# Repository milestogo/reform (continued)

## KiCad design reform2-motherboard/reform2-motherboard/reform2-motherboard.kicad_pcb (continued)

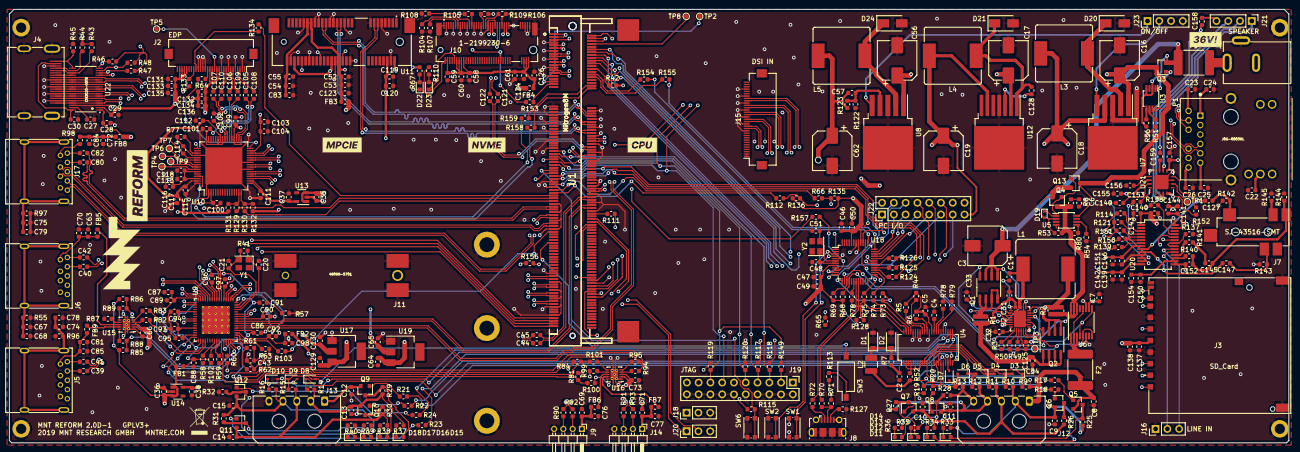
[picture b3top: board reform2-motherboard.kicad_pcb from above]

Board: 6 copper layers, 276.0 x 93.5 mm, 440 parts (0 on the bottom side), 466 nets.

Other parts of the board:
U1#2: Nitrogen8M; TE_1473149-4

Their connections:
+4V: U1#2.1, U1#2.2, U1#2.3, U1#2.4, U1#2.5, U1#2.6; also elsewhere on the board
BACKLIGHT_EN: U1#2.105; also elsewhere on the board
DAC_BCLK: U1#2.170; also elsewhere on the board
DAC_DIN: U1#2.166; also elsewhere on the board
DAC_DOUT: U1#2.178; also elsewhere on the board
DAC_MCLK: U1#2.176; also elsewhere on the board
DAC_RXFS: U1#2.168; also elsewhere on the board
DAC_SCL: U1#2.101; also elsewhere on the board
DAC_SDA: U1#2.103; also elsewhere on the board
DAC_TXFS: U1#2.172; also elsewhere on the board
EDP_SCL: U1#2.107; also elsewhere on the board
EDP_SDA: U1#2.109; also elsewhere on the board
ETH0_A+: U1#2.29; also elsewhere on the board
ETH0_A-: U1#2.27; also elsewhere on the board
ETH0_B+: U1#2.17; also elsewhere on the board
ETH0_B-: U1#2.15; also elsewhere on the board
ETH0_C+: U1#2.23; also elsewhere on the board
ETH0_C-: U1#2.21; also elsewhere on the board
ETH0_D+: U1#2.11; also elsewhere on the board
ETH0_D-: U1#2.9; also elsewhere on the board
ETH0_LED_LINK1: U1#2.83; also elsewhere on the board
ETH0_LED_LINK2: U1#2.81; also elsewhere on the board
ETH0_LED_RX: U1#2.79; also elsewhere on the board
GND: U1#2.7, U1#2.13, U1#2.19, U1#2.25, U1#2.31, U1#2.41, U1#2.44, U1#2.47, U1#2.50, U1#2.53, U1#2.56, U1#2.59, U1#2.62, U1#2.65, U1#2.68, U1#2.71, U1#2.74, U1#2.80, U1#2.94, U1#2.95, U1#2.98, U1#2.99, U1#2.104, U1#2.110, U1#2.111, U1#2.116, U1#2.117, U1#2.123, U1#2.129, U1#2.161, U1#2.167, U1#2.173, U1#2.179, U1#2.185, U1#2.191; also elsewhere on the board
HDMI_CEC: U1#2.197; also elsewhere on the board
HDMI_CLK+: U1#2.165; also elsewhere on the board
HDMI_CLK-: U1#2.163; also elsewhere on the board
HDMI_D0+: U1#2.171; also elsewhere on the board
HDMI_D0-: U1#2.169; also elsewhere on the board
HDMI_D1+: U1#2.177; also elsewhere on the board
HDMI_D1-: U1#2.175; also elsewhere on the board
HDMI_D2+: U1#2.183; also elsewhere on the board
HDMI_D2-: U1#2.181; also elsewhere on the board
HDMI_HPD: U1#2.199; also elsewhere on the board
HDMI_SCL: U1#2.195; also elsewhere on the board
HDMI_SDA: U1#2.193; also elsewhere on the board
IMX_JTAG_TCK: U1#2.73; also elsewhere on the board
IMX_JTAG_TDI: U1#2.75; also elsewhere on the board
IMX_JTAG_TMS: U1#2.77; also elsewhere on the board
IMX_RESETn: U1#2.87; also elsewhere on the board
IMX_UART1_RX: U1#2.126; also elsewhere on the board
IMX_UART1_TX: U1#2.128; also elsewhere on the board
IMX_UART2_RX: U1#2.122; also elsewhere on the board
IMX_UART2_TX: U1#2.124; also elsewhere on the board
LPC_MISO: U1#2.93; also elsewhere on the board
LPC_MOSI: U1#2.91; also elsewhere on the board
LPC_SCK: U1#2.97; also elsewhere on the board
LPC_SS0: U1#2.89; also elsewhere on the board
unnamed 349: U1#2.174; also elsewhere on the board
unnamed 368: U1#2.118; also elsewhere on the board
unnamed 384: U1#2.37; also elsewhere on the board
unnamed 385: U1#2.30; also elsewhere on the board
unnamed 386: U1#2.32; also elsewhere on the board
unnamed 387: U1#2.164; also elsewhere on the board
unnamed 388: U1#2.40; also elsewhere on the board
unnamed 389: U1#2.38; also elsewhere on the board
unnamed 390: U1#2.139; also elsewhere on the board
unnamed 392: U1#2.35; also elsewhere on the board
unnamed 397: U1#2.8; also elsewhere on the board
unnamed 399: U1#2.10; also elsewhere on the board
unnamed 400: U1#2.24; also elsewhere on the board
unnamed 401: U1#2.28; also elsewhere on the board
unnamed 402: U1#2.33; also elsewhere on the board
unnamed 403: U1#2.34; also elsewhere on the board
unnamed 404: U1#2.36; also elsewhere on the board
unnamed 405: U1#2.39; also elsewhere on the board
unnamed 406: U1#2.42; also elsewhere on the board
unnamed 407: U1#2.43; also elsewhere on the board
unnamed 408: U1#2.45; also elsewhere on the board
unnamed 409: U1#2.49; also elsewhere on the board
unnamed 410: U1#2.51; also elsewhere on the board
unnamed 411: U1#2.55; also elsewhere on the board
unnamed 412: U1#2.57; also elsewhere on the board
unnamed 413: U1#2.61; also elsewhere on the board
unnamed 414: U1#2.63; also elsewhere on the board
unnamed 415: U1#2.67; also elsewhere on the board
unnamed 416: U1#2.69; also elsewhere on the board
unnamed 417: U1#2.82; also elsewhere on the board
unnamed 418: U1#2.84; also elsewhere on the board
unnamed 419: U1#2.85; also elsewhere on the board
unnamed 420: U1#2.86; also elsewhere on the board
unnamed 421: U1#2.88; also elsewhere on the board
unnamed 422: U1#2.90; also elsewhere on the board
unnamed 423: U1#2.92; also elsewhere on the board
unnamed 424: U1#2.96; also elsewhere on the board
unnamed 425: U1#2.120; also elsewhere on the board
unnamed 426: U1#2.130; also elsewhere on the board
unnamed 427: U1#2.132; also elsewhere on the board
unnamed 428: U1#2.133; also elsewhere on the board
unnamed 429: U1#2.134; also elsewhere on the board
unnamed 430: U1#2.135; also elsewhere on the board
unnamed 431: U1#2.136; also elsewhere on the board
unnamed 432: U1#2.137; also elsewhere on the board
unnamed 433: U1#2.138; also elsewhere on the board
unnamed 434: U1#2.140; also elsewhere on the board
unnamed 435: U1#2.141; also elsewhere on the board
unnamed 436: U1#2.142; also elsewhere on the board
unnamed 437: U1#2.143; also elsewhere on the board
unnamed 438: U1#2.144; also elsewhere on the board
unnamed 439: U1#2.145; also elsewhere on the board
unnamed 440: U1#2.146; also elsewhere on the board
unnamed 441: U1#2.147; also elsewhere on the board
unnamed 442: U1#2.148; also elsewhere on the board
unnamed 443: U1#2.149; also elsewhere on the board
unnamed 444: U1#2.150; also elsewhere on the board
unnamed 445: U1#2.151; also elsewhere on the board
unnamed 446: U1#2.152; also elsewhere on the board
unnamed 447: U1#2.153; also elsewhere on the board
unnamed 448: U1#2.154; also elsewhere on the board
unnamed 449: U1#2.155; also elsewhere on the board
unnamed 450: U1#2.156; also elsewhere on the board
unnamed 451: U1#2.157; also elsewhere on the board
unnamed 452: U1#2.158; also elsewhere on the board
unnamed 453: U1#2.159; also elsewhere on the board
unnamed 454: U1#2.160; also elsewhere on the board
unnamed 455: U1#2.162; also elsewhere on the board
unnamed 456: U1#2.180; also elsewhere on the board
unnamed 457: U1#2.182; also elsewhere on the board
unnamed 458: U1#2.184; also elsewhere on the board
unnamed 459: U1#2.186; also elsewhere on the board
unnamed 460: U1#2.187; also elsewhere on the board
unnamed 461: U1#2.188; also elsewhere on the board
unnamed 462: U1#2.189; also elsewhere on the board
unnamed 463: U1#2.190; also elsewhere on the board
unnamed 464: U1#2.192; also elsewhere on the board
unnamed 465: U1#2.194; also elsewhere on the board
unnamed 466: U1#2.196; also elsewhere on the board
unnamed 467: U1#2.198; also elsewhere on the board
unnamed 468: U1#2.200; also elsewhere on the board
PCIE1_CLK_N: U1#2.60; also elsewhere on the board
PCIE1_CLK_P: U1#2.58; also elsewhere on the board
PCIE1_RX_N: U1#2.54; also elsewhere on the board
PCIE1_RX_P: U1#2.52; also elsewhere on the board
PCIE1_TX_N: U1#2.48; also elsewhere on the board
PCIE1_TX_P: U1#2.46; also elsewhere on the board
PCIE2_CLK_N: U1#2.66; also elsewhere on the board
PCIE2_CLK_P: U1#2.64; also elsewhere on the board
PCIE2_RX_N: U1#2.78; also elsewhere on the board
PCIE2_RX_P: U1#2.76; also elsewhere on the board
PCIE2_TX_N: U1#2.72; also elsewhere on the board
PCIE2_TX_P: U1#2.70; also elsewhere on the board
SD2_CD: U1#2.26; also elsewhere on the board
SD2_CLK: U1#2.22; also elsewhere on the board
SD2_CMD: U1#2.20; also elsewhere on the board
SD2_DATA0: U1#2.12; also elsewhere on the board
SD2_DATA1: U1#2.14; also elsewhere on the board
SD2_DATA2: U1#2.16; also elsewhere on the board
SD2_DATA3: U1#2.18; also elsewhere on the board
USB1_DN: U1#2.100; also elsewhere on the board
USB1_DP: U1#2.102; also elsewhere on the board
USB1_RX_N: U1#2.112; also elsewhere on the board
USB1_RX_P: U1#2.114; also elsewhere on the board
USB1_TX_N: U1#2.106; also elsewhere on the board
USB1_TX_P: U1#2.108; also elsewhere on the board
USB2_DN: U1#2.125; also elsewhere on the board
USB2_DP: U1#2.127; also elsewhere on the board
USB2_RX_N: U1#2.121; also elsewhere on the board
USB2_RX_P: U1#2.119; also elsewhere on the board
USB2_TX_N: U1#2.115; also elsewhere on the board
USB2_TX_P: U1#2.113; also elsewhere on the board
USB_RESETn: U1#2.131; also elsewhere on the board

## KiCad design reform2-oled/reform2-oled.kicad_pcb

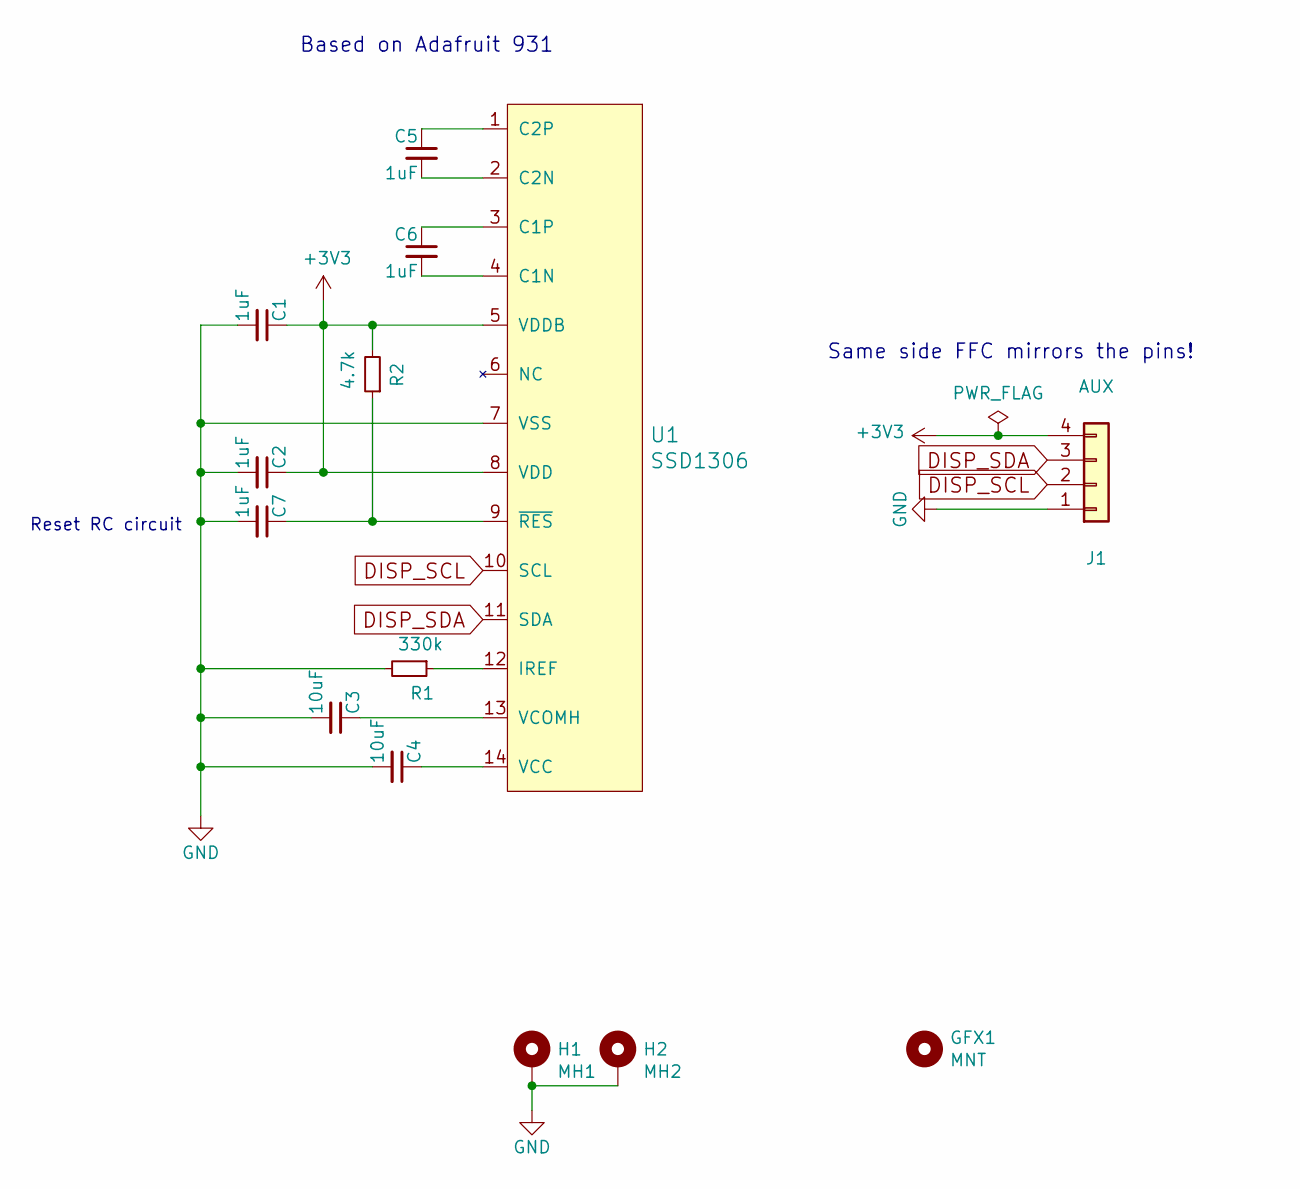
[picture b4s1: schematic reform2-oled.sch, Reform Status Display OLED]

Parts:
C1, C2, C5, C6, C7: 1uF; C_0603_1608Metric_Pad1.05x0.95mm_HandSolder
C3, C4: 10uF; C_0603_1608Metric_Pad1.05x0.95mm_HandSolder
GFX1: MNT; mntreform
H1: MH1; MountingHole_2.2mm_M2_Pad
H2: MH2; MountingHole_2.2mm_M2_Pad
J1: AUX; Molex_200528-0040_1x04-1MP_P1.00mm_Horizontal
R1: 330k; R_0603_1608Metric_Pad1.05x0.95mm_HandSolder
R2: 4.7k; R_0603_1608Metric_Pad1.05x0.95mm_HandSolder
U1: SSD1306; SSD1306_OLED-0.91-128x32

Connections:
+3V3: C1.1, C2.1, J1.4, R2.2, U1.5 (VDDB), U1.8 (VDD)
DISP_SCL: J1.2, U1.10 (SCL)
DISP_SDA: J1.3, U1.11 (SDA)
GND: C1.2, C2.2, C3.2, C4.2, C7.2, H1.1, H2.1, J1.1, R1.2, U1.7 (VSS)
unnamed: C3.1, U1.13 (VCOMH)
unnamed: C4.1, U1.14 (VCC)
unnamed: C5.1, U1.1 (C2P)
unnamed: C5.2, U1.2 (C2N)
unnamed: C6.1, U1.3 (C1P)
unnamed: C6.2, U1.4 (C1N)
unnamed: C7.1, R2.1, U1.9 (~RES)
unnamed: R1.1, U1.12 (IREF)

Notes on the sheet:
Based on Adafruit 931
Reset RC circuit
Same side FFC mirrors the pins!

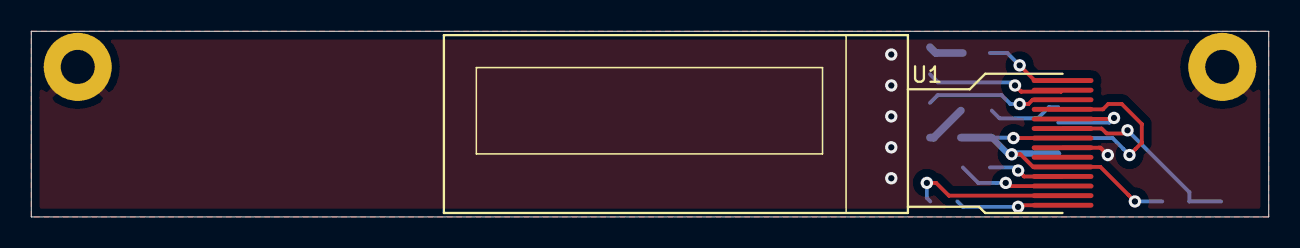
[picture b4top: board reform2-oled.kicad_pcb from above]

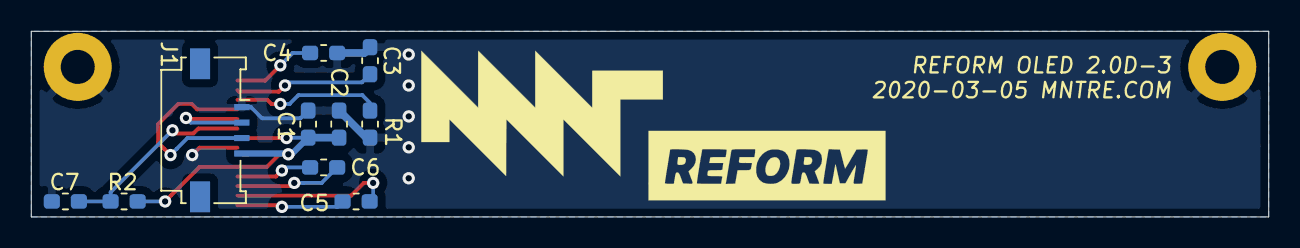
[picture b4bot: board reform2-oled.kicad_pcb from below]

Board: 2 copper layers, 80.0 x 12.0 mm, 14 parts (11 on the bottom side), 12 nets.

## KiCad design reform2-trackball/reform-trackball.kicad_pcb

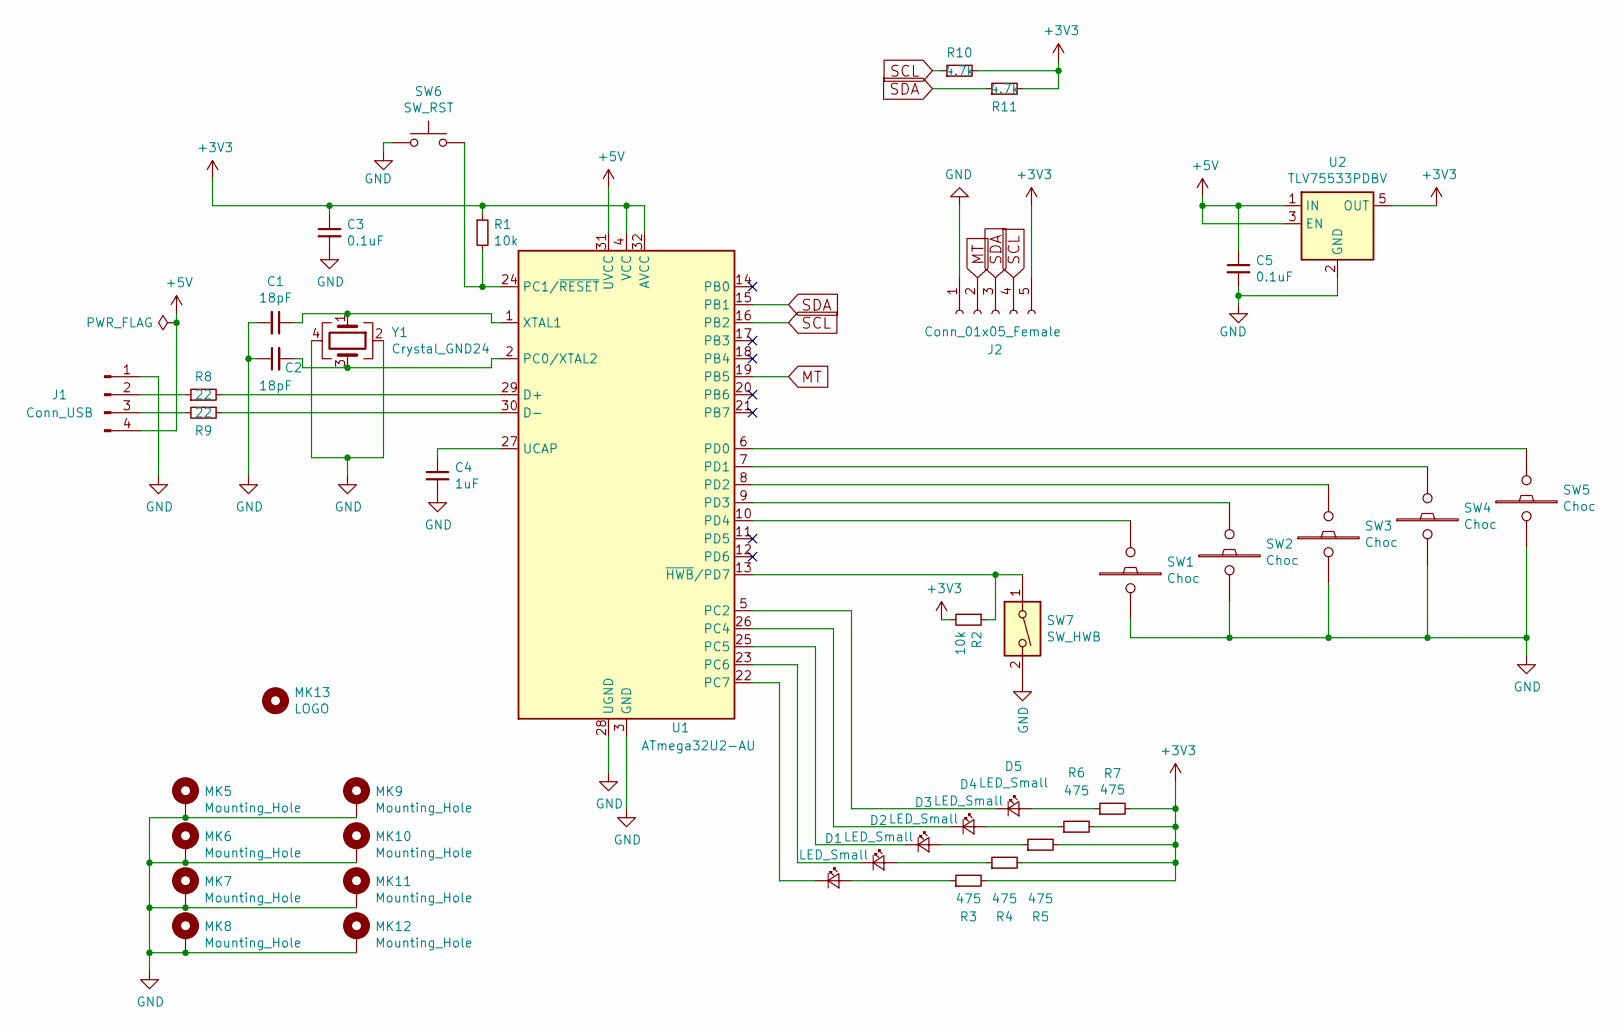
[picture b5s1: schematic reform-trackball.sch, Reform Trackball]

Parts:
C1, C2: 18pF; C_0603_1608Metric
C3, C5: 0.1uF; C_0603_1608Metric
C4: 1uF; C_0603_1608Metric
D1, D2, D3, D4, D5: LED_Small; LED_0603_1608Metric
J1: Conn_USB; Pin_Header_Straight_1x04_Pitch2.00mm
J2: Conn_01x05_Female; PinSocket_1x05_P2.54mm_Vertical
MK5, MK6, MK7, MK8, MK9, MK10, MK11, MK12: Mounting_Hole; MountingHole_2.2mm_M2_Pad
MK13: LOGO; mntreform
R1, R2: 10k; R_0603_1608Metric
R3, R4, R5, R6, R7: 475; R_0603_1608Metric
R8, R9: 22; R_0603_1608Metric
R10, R11: 4.7k; R_0603_1608Metric
SW1, SW2, SW3, SW4, SW5: Choc; PG1350
SW6: SW_RST; SW_Push_1P1T_NO_CK_KMR2
SW7: SW_HWB; SW_DIP_SPSTx01_Slide_Omron_A6S-110x_W8.9mm_P2.54mm
U1: ATmega32U2-AU; TQFP-32_7x7mm_Pitch0.8mm
U2: TLV75533PDBV; SOT-23-5
Y1: Crystal_GND24; Crystal_SMD_3225-4pin_3.2x2.5mm_HandSoldering

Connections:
+3V3: C3.1, J2.5, R1.1, R2.2, R3.2, R4.2, R5.2, R6.2, R7.2, R10.2, R11.2, U1.4 (VCC), U1.32 (AVCC), U2.5 (OUT)
+5V: C5.1, J1.4, U1.31 (UVCC), U2.1 (IN), U2.3 (EN)
GND: C1.2, C2.1, C3.2, C4.2, C5.2, J1.1, J2.1, MK5.1, MK6.1, MK7.1, MK8.1, MK9.1, MK10.1, MK11.1, MK12.1, SW1.2, SW2.2, SW3.2, SW4.2, SW5.2, SW6.1, SW7.2, U1.3 (GND), U1.28 (UGND), U2.2 (GND), Y1.2, Y1.4
MT: J2.2, U1.19 (PB5)
unnamed: C1.1, U1.1 (XTAL1), Y1.1
unnamed: C2.2, U1.2 (PC0/XTAL2), Y1.3
unnamed: C4.1, U1.27 (UCAP)
unnamed: D1.1 (K), U1.22 (PC7)
unnamed: D1.2 (A), R3.1
unnamed: D2.1 (K), U1.23 (PC6)
unnamed: D2.2 (A), R4.1
unnamed: D3.1 (K), U1.25 (PC5)
unnamed: D3.2 (A), R5.1
unnamed: D4.1 (K), U1.26 (PC4)
unnamed: D4.2 (A), R6.1
unnamed: D5.1 (K), U1.5 (PC2)
unnamed: D5.2 (A), R7.1
unnamed: J1.2, R8.1
unnamed: J1.3, R9.2
unnamed: R1.2, SW6.2, U1.24 (PC1/~RESET)
unnamed: R2.1, SW7.1, U1.13 (~HWB~/PD7)
unnamed: R8.2, U1.29 (D+)
unnamed: R9.1, U1.30 (D-)
unnamed: SW1.1, U1.10 (PD4)
unnamed: SW2.1, U1.9 (PD3)
unnamed: SW3.1, U1.8 (PD2)
unnamed: SW4.1, U1.7 (PD1)
unnamed: SW5.1, U1.6 (PD0)
SCL: J2.4, R10.1, U1.16 (PB2)
SDA: J2.3, R11.1, U1.15 (PB1)

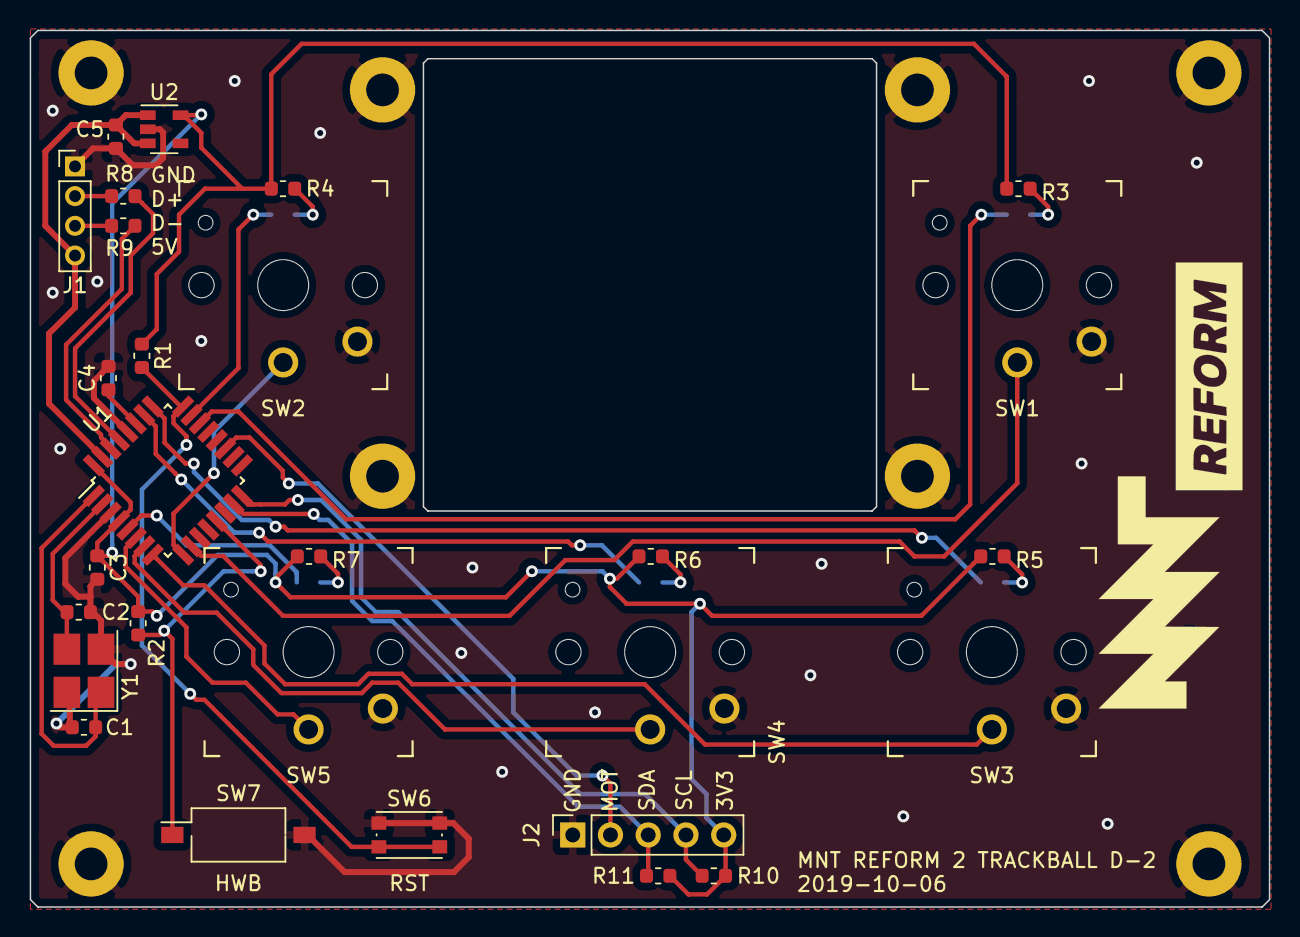
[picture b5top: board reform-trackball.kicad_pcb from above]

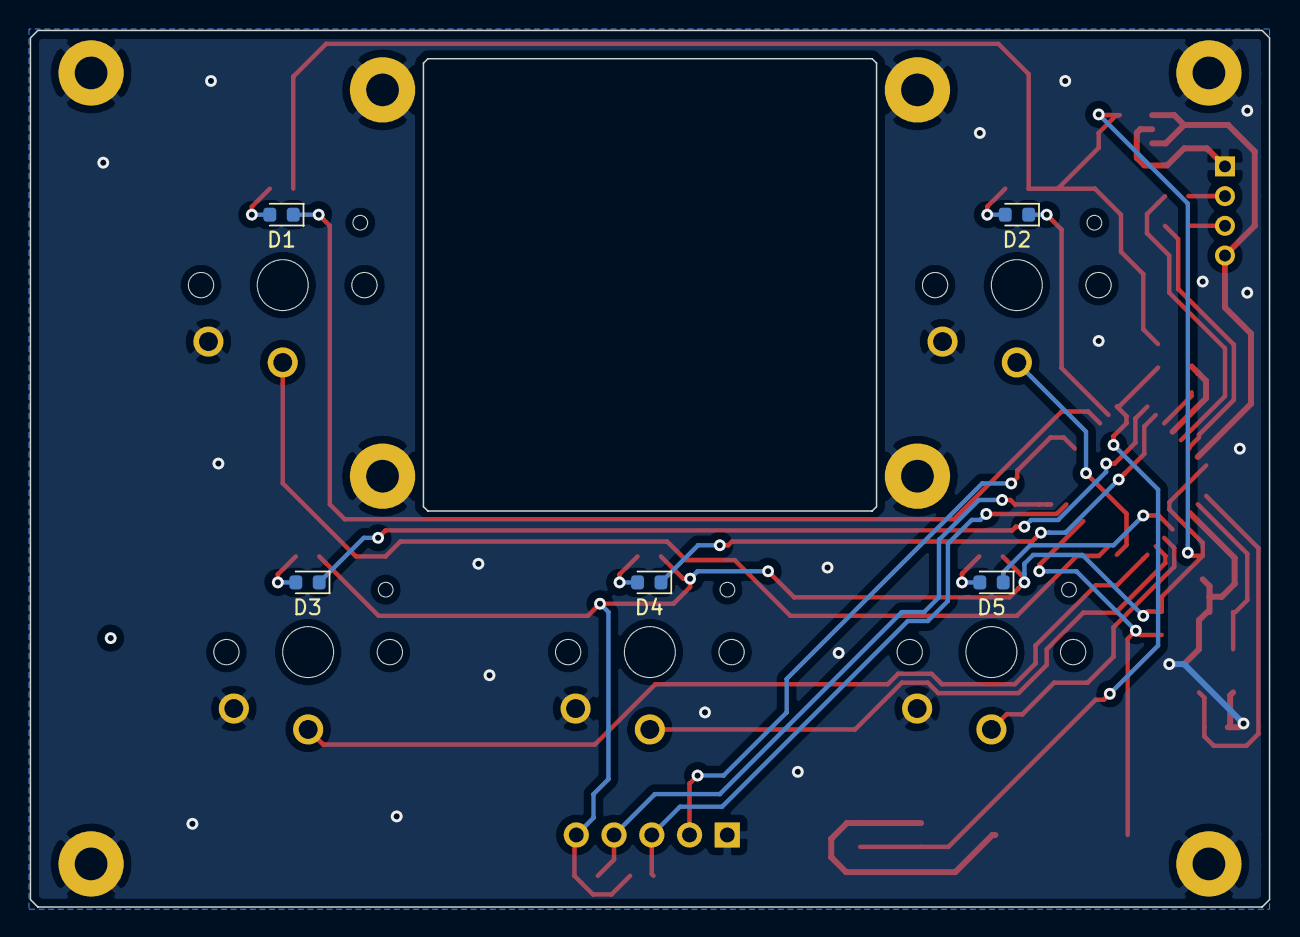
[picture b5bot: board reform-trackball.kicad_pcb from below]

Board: 2 copper layers, 83.4 x 59.0 mm, 42 parts (10 on the bottom side), 30 nets.
